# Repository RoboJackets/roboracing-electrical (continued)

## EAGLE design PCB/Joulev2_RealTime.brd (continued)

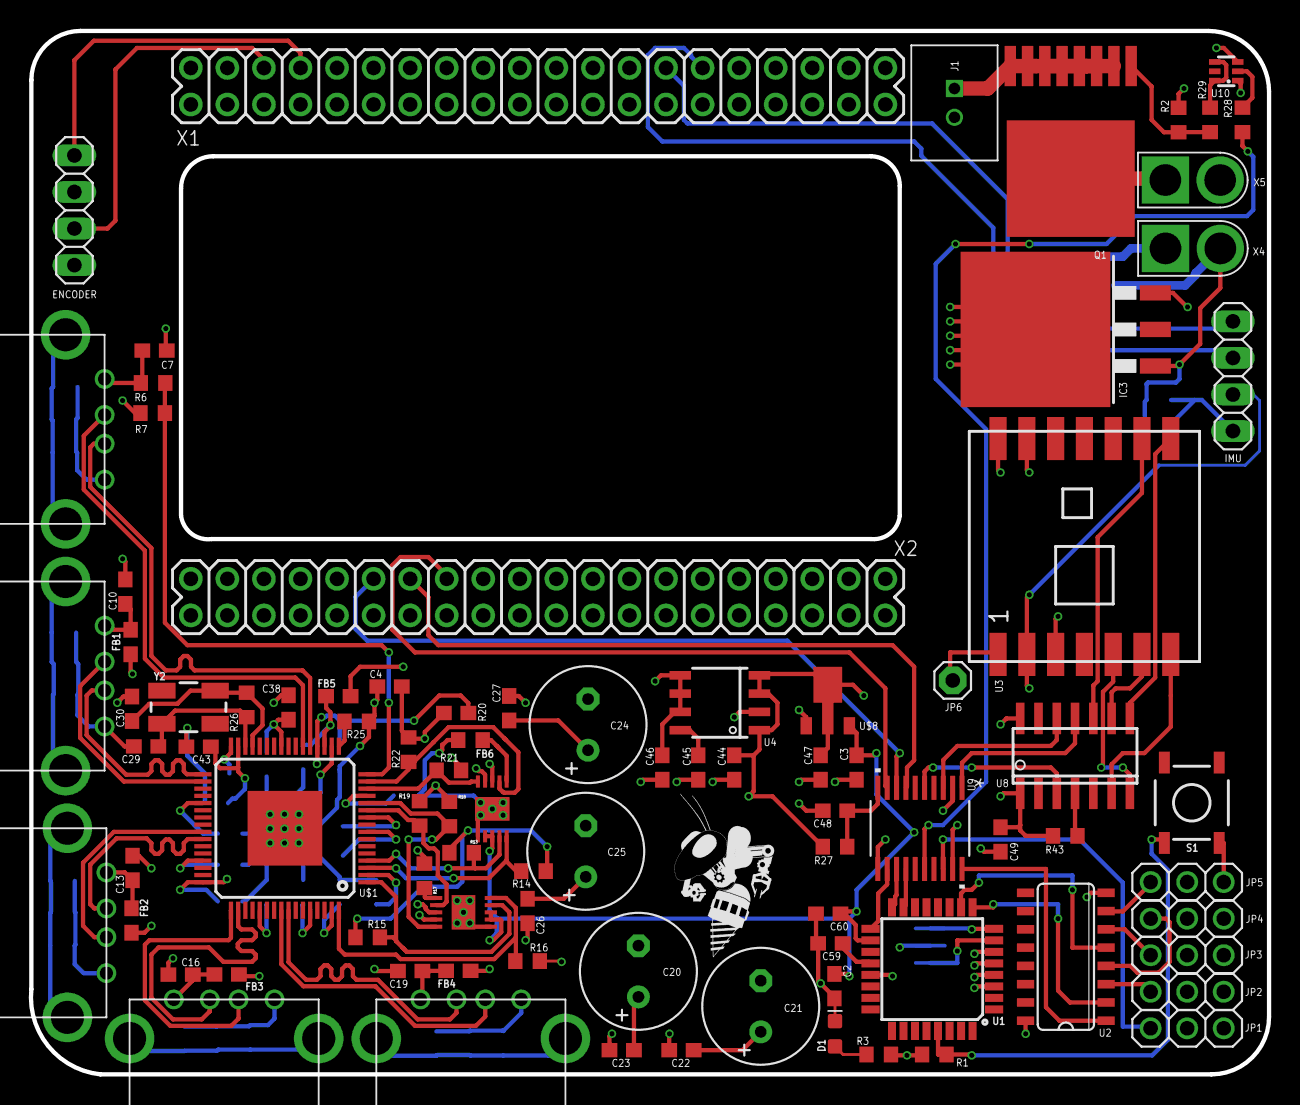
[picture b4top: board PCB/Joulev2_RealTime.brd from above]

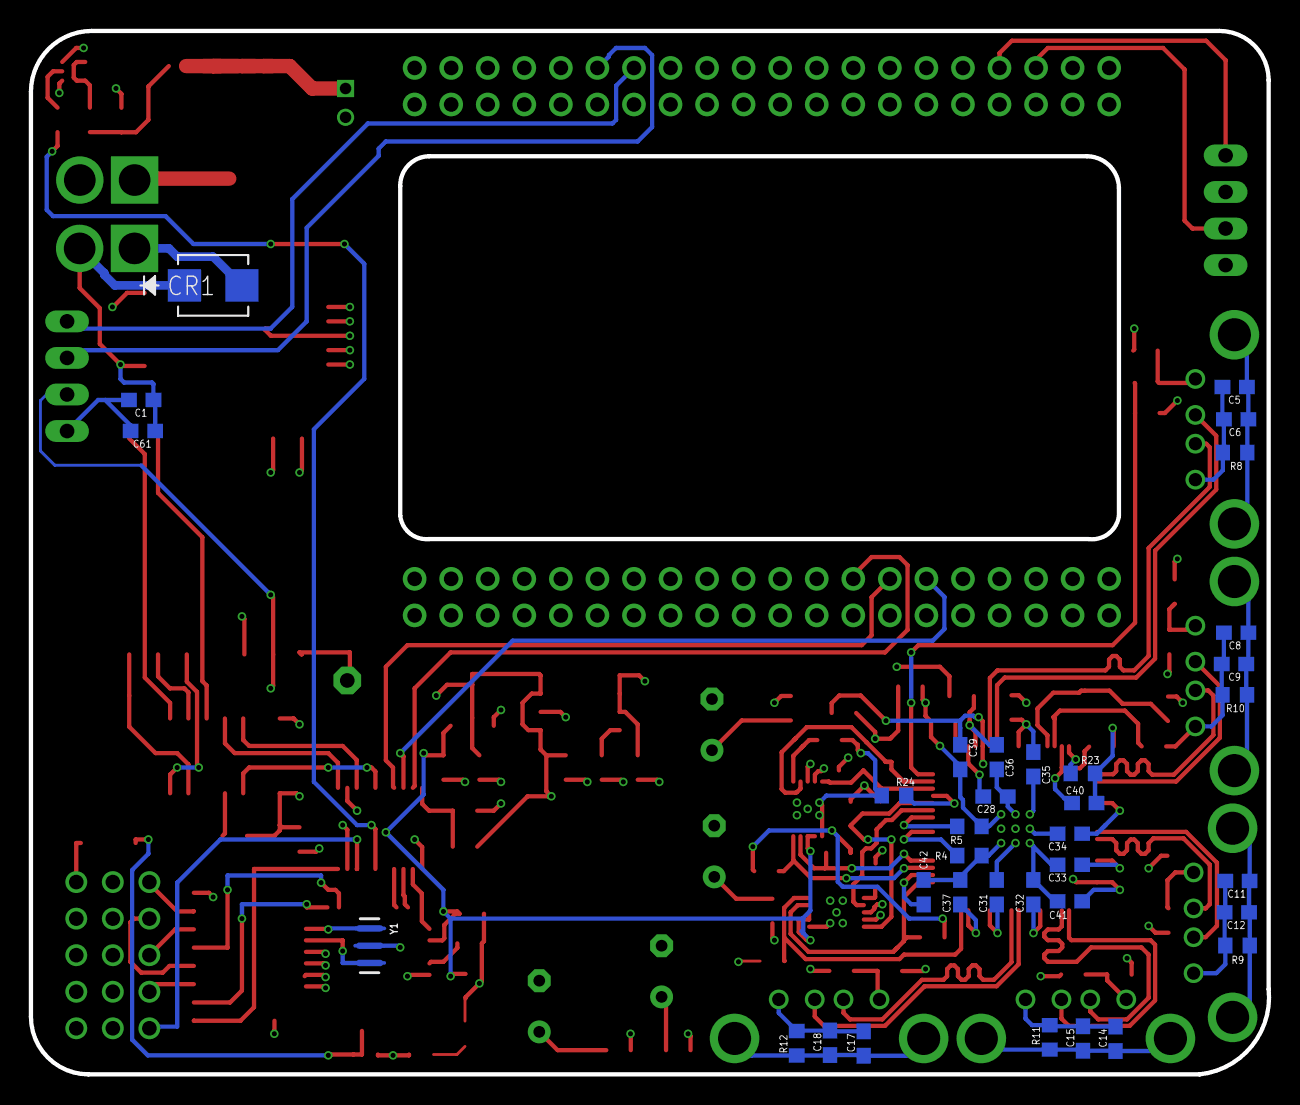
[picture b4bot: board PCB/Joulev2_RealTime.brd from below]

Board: 4 copper layers, 86.0 x 72.5 mm, 125 parts (35 on the bottom side), 94 nets.

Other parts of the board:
U$9: ROBOBUZZ_0.6X

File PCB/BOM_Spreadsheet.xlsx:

Qty | Value | Device | Package | Parts | Description | MANUFACTURER_PART_NUMBER | PINS | PIN_PITCH | PROD_ID | SF_ID | SF_SKU | VALUE | VENDOR | VENDOR PART# | LINK | COST | TOT COST | Notes
3 |  | LED0603 | LED-0603 | D1 | LED (Generic) | LS Q976-NR-1 |  |  |  |  |  |  | Digikey | 475-2512-1-ND | https://www.digikey.com/product-detail/en/osram-opto-semicon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 | 0.26 | 0.78 | Spare 2 ordered
10 |  | PINHD-1X3 | 1X03 | 1, 2, 3, SER, THR | PIN HEADER | M20-9990345 |  |  |  |  |  |  | Digikey | 952-2263-ND | https://www.digikey.com/product-detail/en/harwin-inc/M20-999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 | 0.18 | 1.7999999999999998 | Spare 5 Ordered
5 |  | PINHD-1X4 | 1X04 | ENCODER, IMU | PIN HEADER | 68016-204HLF |  |  |  |  |  |  | Digikey | 609-3319-ND | https://www.digikey.com/product-detail/en/amphenol-fci/68016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 | 0.31 | 1.55 | Spare 3 ordered
40 | 0.1uF | C-USC0603 | C0603 | C2, C5, C9, C10, C12, C13, C15, C16, C18, C19, C22, C23, C26, C27, C28, C31, C3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 | CAPACITOR, American symbol | GRM033R61A104ME15D |  |  |  |  |  |  | Digikey | 490-5405-6-ND | https://www.digikey.com/product-detail/en/murata-electronics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 | 0.17 | 6.8000000000000007 | Spare 11 ordered
3 | 0.22uF | C-USC0603 | C0603 | C1 | CAPACITOR, American symbol | C1608X7R1C224K080AC |  |  |  |  |  |  | Digikey | 445-1318-1-ND | https://www.digikey.com/product-detail/en/tdk-corporation/C1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 | 0.1 | 0.30000000000000004 | Spare 2 ordered
10 | 1.0nF | C-USC0603 | C0603 | C6 | CAPACITOR, American symbol | GRM155R60J102KA01D |  |  |  |  |  |  | Digikey | 490-6285-1-ND | https://www.digikey.com/product-detail/en/murata-electronics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 | 1.0999999999999999E-2 | 0.10999999999999999 | Spare 9 ordered (cheaper than just 3)
10 | 10 | R-US_R0603 | R0603 | R29 | RESISTOR, American symbol | RC0603FR-0710RL |  |  |  |  |  |  | Digikey | 311-10.0HRCT-ND | https://www.digikey.com/product-detail/en/yageo/RC0603FR-071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 | 1.4E-2 | 0.14000000000000001 | Spare 9 ordered (cheaper than just 3)
10 | 10nF | C-USC0603 | C0603 | C45 | CAPACITOR, American symbol | GRM033R71A103KA01D |  |  |  |  |  |  | Digikey | 490-3194-1-ND | https://www.digikey.com/product-detail/en/murata-electronics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 | 2.1000000000000001E-2 | 0.21000000000000002 | Spare 9 ordered (cheaper than just 3)
4 | 1000pF | C-USC0603 | C0603 | C8, C11, C14, C17 | CAPACITOR, American symbol |  |  |  |  |  |  |  | Digikey |  |  |  | 0
9 | 10k | R-US_R0603 | R0603 | R1, R2, R7, R18, R19, R21, R22, R27, R43 | RESISTOR, American symbol |  |  |  |  |  |  |  | Digikey |  |  |  | 0
6 | 10uF | C-USC0603 | C0603 | C3, C4, C7, C38, C43, C61 | CAPACITOR, American symbol |  |  |  |  |  |  |  | Digikey |  |  |  | 0
4 | 150uF | CPOL-USE3.5-8 | E3,5-8 | C20, C21, C24, C25 | POLARIZED CAPACITOR, American symbol |  |  |  |  |  |  |  | Digikey |  |  |  | 0
1 | 16MHz | RESONATOR-16MHZSMD_3.2X1.3 | RESONATOR-SMD-3.2X1.3 | Y1 | 16MHz Resonator |  |  |  | XTAL-08900 |  |  | 16MHz | Digikey |  |  |  | 0
2 | 18pF | C-USC0603 | C0603 | C29, C30 | CAPACITOR, American symbol |  |  |  |  |  |  |  | Digikey |  |  |  | 0
6 | 1M | R-US_R0603 | R0603 | R8, R9, R10, R11, R12, R26 | RESISTOR, American symbol |  |  |  |  |  |  |  | Digikey |  |  |  | 0
1 | 1uF | C-USC0603 | C0603 | C48 | CAPACITOR, American symbol |  |  |  |  |  |  |  | Digikey |  |  |  | 0
1 | 2-PIN_2MM-V | 2-PIN_2MM-V | 2MM-2-V | J1 |  |  | 2 | 2.0 mm |  |  |  |  |  |  |  |  | 0
6 | 220@100MHz | FERRITE_BEAD-0603 | 603 | FB1, FB2, FB3, FB4, FB5, FB6 | Ferrite Bead (blocks, cores, rings, chokes, etc.) |  |  |  | NDUC-07859 |  |  | 30O/1.8A |  |  |  |  | 0
1 | 22uF | C-USC0603 | C0603 | C47 | CAPACITOR, American symbol |  |  |  |  |  |  |  |  |  |  |  | 0
1 | 24MHz | CRYSTAL-24MHZ";CRYSTAL-SMD-5X3.2-4PAD" | Y2 | 24MHz Crystal |  |  |  | XTAL-08298 | COM-08581 |  | 24MHz |  |  |  |  |  | 0
2 | 25.5k | R-US_R0603 | R0603 | R17, R20 | RESISTOR, American symbol |  |  |  |  |  |  |  |  |  |  |  | 0
8 | 4.7k | R-US_R0603 | R0603 | R4, R5, R13, R14, R15, R16, R24, R25 | RESISTOR, American symbol |  |  |  |  |  |  |  |  |  |  |  | 0
2 | 4.7uF | C-USC0603 | C0603 | C44, C46 | CAPACITOR, American symbol |  |  |  |  |  |  |  |  |  |  |  | 0
1 | 500 | R-US_R0603 | R0603 | R28 | RESISTOR, American symbol |  |  |  |  |  |  |  |  |  |  |  | 0
1 | 680 | R-US_R0603 | R0603 | R3 | RESISTOR, American symbol |  |  |  |  |  |  |  |  |  |  |  | 0
1 | 74VHC_MUXSO16 | 74VHC_MUXSO16 | SO16 | U2 |  |  |  |  |  |  |  |  |  |  |  |  | 0
1 | 9.53k | R-US_R0603 | R0603 | R23 | RESISTOR, American symbol |  |  |  |  |  |  |  |  |  |  |  | 0
1 | 90.9k | R-US_R0603 | R0603 | R6 | RESISTOR, American symbol |  |  |  |  |  |  |  |  |  |  |  | 0
1 | ADP1706ARDZ-1.1-R7 | ADP1706ARDZ-1.1-R7 | SOIC8 | U4 |  |  |  |  |  |  |  |  |  |  |  |  | 0
1 | ATMEGA328P_TQFP | ATMEGA328P_TQFP | TQFP32-08 | U1 | Popular 328P in QFP |  |  |  | IC-09069 |  |  | ATMEGA328P_TQFP |  |  |  |  | 0
1 | ATTINY441/841SSU/SSUR | ATTINY441/841SSU/SSUR | SOIC-14 | U8 |  |  |  |  |  |  |  |  |  |  |  |  | 0
1 | AZ1117CR-3.3TRG1DICT-ND | AZ1117CR-3.3TRG1DICT-ND | SOT89R_INFINEON | U$8 |  |  |  |  |  |  |  |  |  |  |  |  | 0
1 | J12HEADER_(JOULE) | J12HEADER_(JOULE) | 2X20 | X1 |  |  |  |  |  |  |  |  |  |  |  |  | 0
1 | J13HEADER_(JOULE) | J13HEADER_(JOULE) | 2X20 | X2 |  |  |  |  |  |  |  |  |  |  |  |  | 0
1 | LM340S-05 | LM340S-05 | TO263-3 | IC3 | Positive VOLTAGE REGULATOR |  |  |  |  |  |  |  |  |  |  |  | 0
1 | MOMENTARY-SWITCH 5.2mm | MOMENTARY-SWITCH-SPST-SMD-5.2MM | TACTILE_SWITCH_SMD_5.2MM | S1 | Momentary Switch (Pushbutton) - SPST |  |  |  | SWCH-08247 |  | COM-08720 |  |  |  |  |  | 0
1 | N_CH_MOSFET_FDLBL260N100 | N_CH_MOSFET_FDLBL260N100 | MO-299A | Q1 |  |  |  |  |  |  |  |  |  |  |  |  | 0
1 | RFM69CW | RFM69CW | RFM69CW-XXXS2 | U3 |  |  |  |  |  |  |  |  |  |  |  |  | 0
1 | SMBJ13CA | SMBJ13CA | SMB | CR1 |  | SMBJ13CA |  |  |  |  |  |  | Bourns Electronics |  |  |  | 0
2 | TPS2561DRCT | TPS2561DRCT | 10-VSON | U$10, U$11 |  |  |  |  |  |  |  |  |  |  |  |  | 0
2 | TRAXXAS-CON | TRAXXAS-CON | TRAXXAS-CON | X4, X5 |  |  |  |  |  |  |  |  |  |  |  |  | 0
1 | TUSB4041 | TUSB4041 | TQFP64-10X10 | U$1 |  |  |  |  |  |  |  |  |  |  |  |  | 0
1 | TXB0108PWR | TXB0108PWR | PW20 | U9 |  | TXB0108PWR |  |  |  |  |  |  | Texas Instruments |  |  |  | 0
5 | USB_TYPE_A | USB_TYPE_A | USB_TYPE_A | U$3, U$4, U$5, U$6, U$7 |  |  |  |  |  |  |  |  |  |  |  |  | 0
1 | ZXGD3009DY | ZXGD3009DY | SOT363 | U10 |  |  |  |  |  |  |  |  |  |  |  |  | 0
1 | antenna | PINHD-1X1 | 1X01 | JP6 | Pin header 1x1 for 0.1 spacing" |  |  |  |  |  |  |  |  |  |  |  | 0

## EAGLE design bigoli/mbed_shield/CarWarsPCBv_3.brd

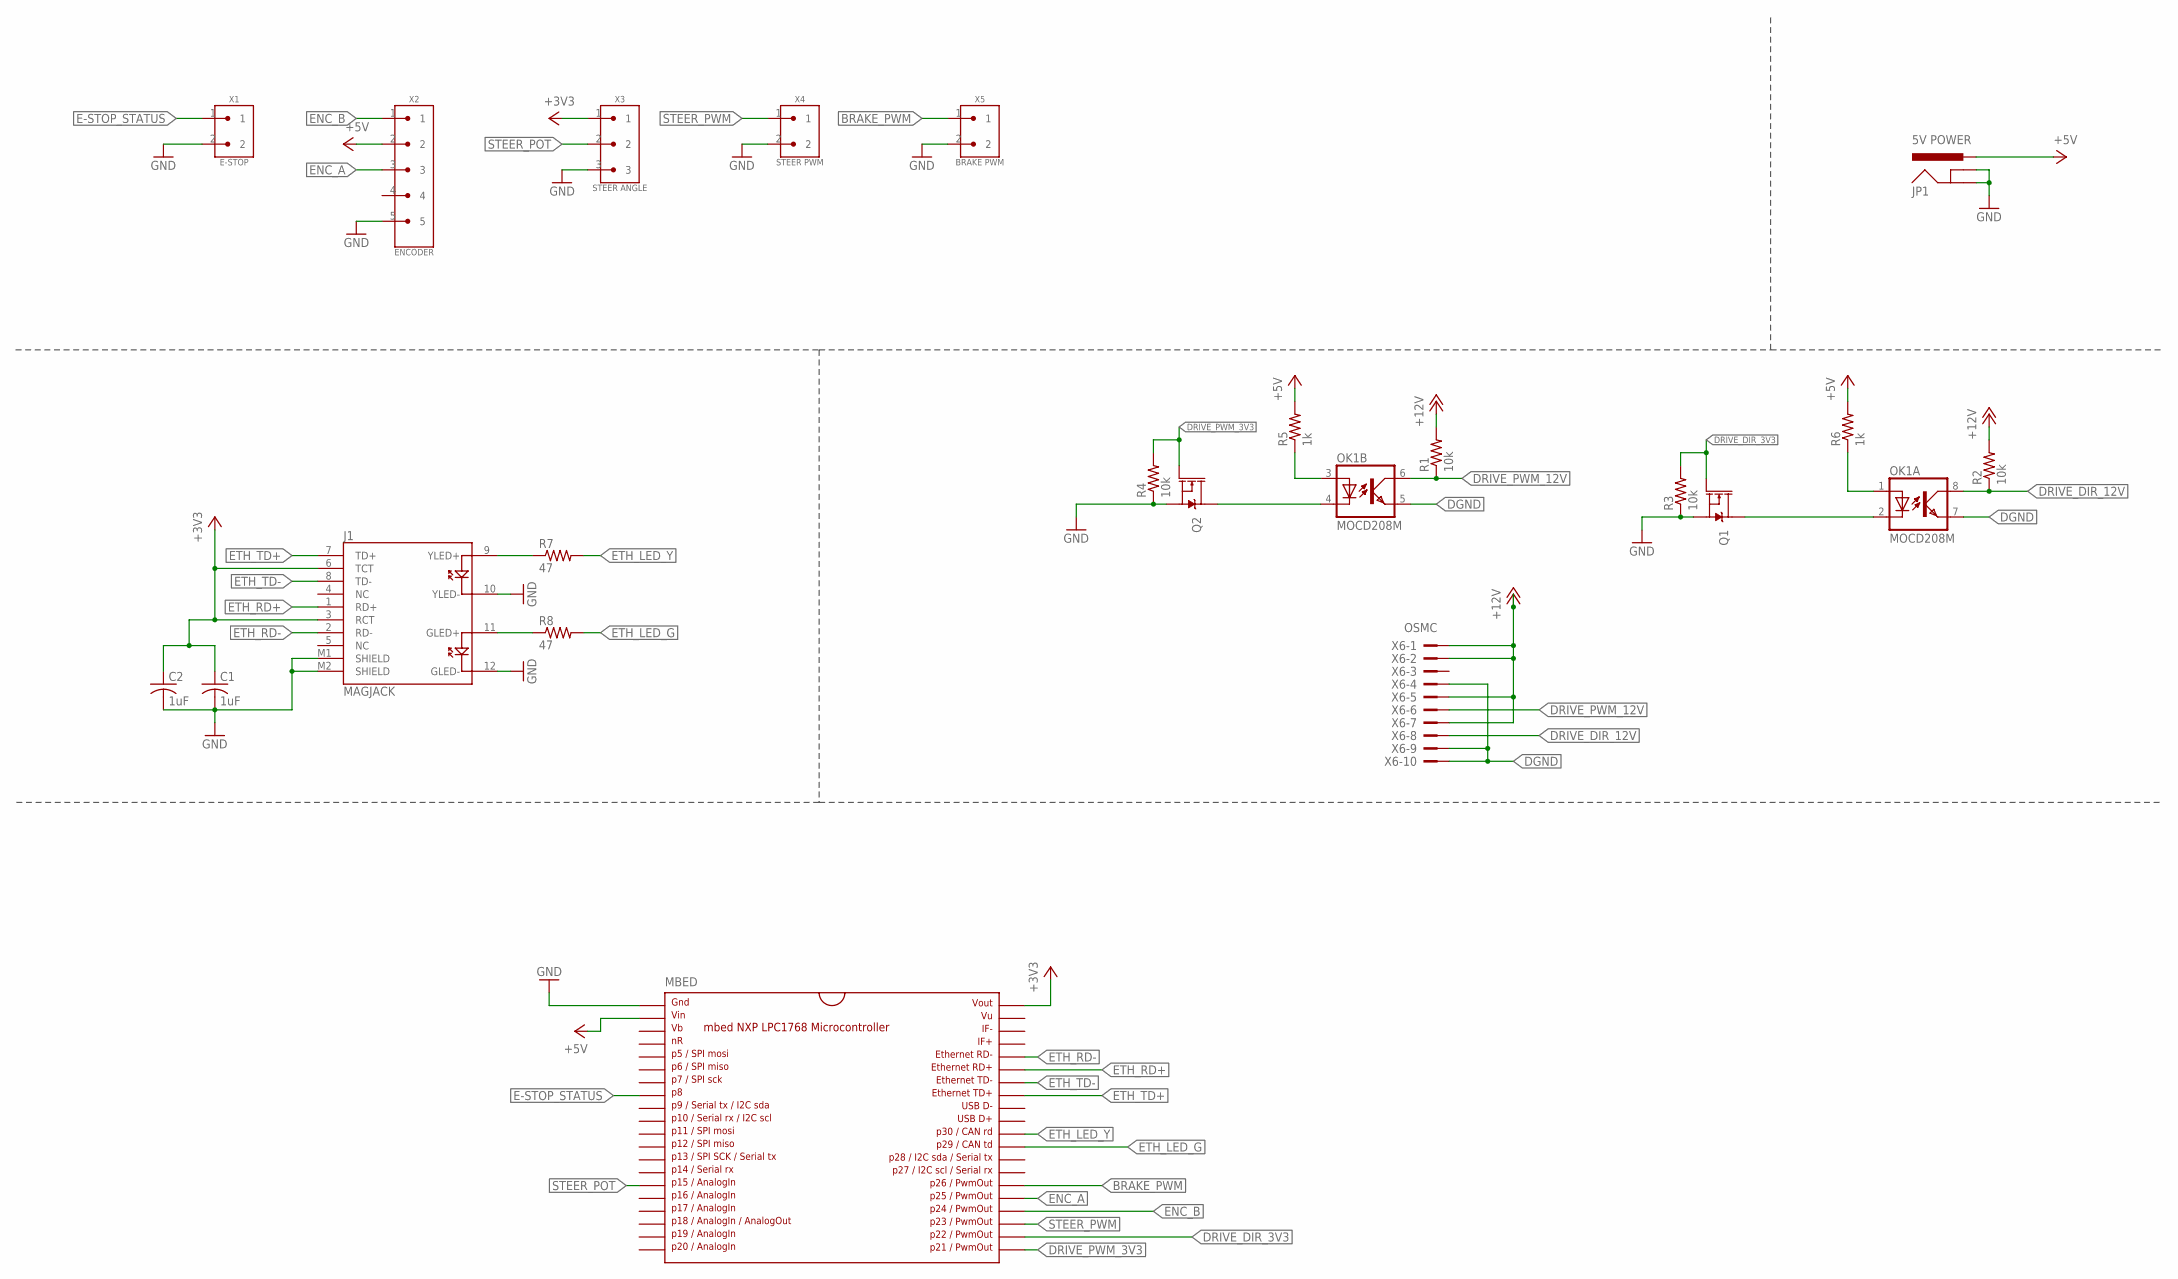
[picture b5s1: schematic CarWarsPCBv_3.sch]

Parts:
C1, C2: 1uF; C0805
J1: MAGJACK
JP1: 5V POWER; POWER_JACK_PTH
MBED: MBED1768; DIL40_0.9
OK1: MOCD208M; SOIC08-FAIRCHILD
Q1, Q2: MOSFET-NCH-BSS138; SOT23-3
R1, R2, R3, R4: 10k; R0603
R5, R6: 1k; R0603
R7, R8: 47; R0603
X1: E-STOP; S2B-EH
X2: ENCODER; S5B-EH
X3: STEER ANGLE; S3B-EH
X4: STEER PWM; S2B-EH
X5: BRAKE PWM; S2B-EH
X6: OSMC; PAK100/2500-10

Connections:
+3V3: C1.1, C2.1, J1.3 (RCT), J1.6 (TCT), MBED.40, X3.1
+5V: JP1.PWR, MBED.2, R5.2, R6.2, X2.2
+12V: R1.2, R2.2, X6.1, X6.2, X6.5, X6.7
BRAKE_PWM: MBED.26, X5.1
DGND: OK1.5 (EMIT), OK1.7 (EMIT), X6.4, X6.9, X6.10
DRIVE_DIR_3V3: MBED.22, Q1.1 (G), R3.2
DRIVE_DIR_12V: OK1.8 (COL), R2.1, X6.8
DRIVE_PWM_3V3: MBED.21, Q2.1 (G), R4.2
DRIVE_PWM_12V: OK1.6 (COL), R1.1, X6.6
E-STOP_STATUS: MBED.8, X1.1
ENC_A: MBED.25, X2.3
ENC_B: MBED.24, X2.1
ETH_LED_G: MBED.29, R8.2
ETH_LED_Y: MBED.30, R7.2
ETH_RD+: J1.1 (RD+), MBED.35
ETH_RD-: J1.2 (RD-), MBED.36
ETH_TD+: J1.7 (TD+), MBED.33
ETH_TD-: J1.8 (TD-), MBED.34
GND: C1.2, C2.2, J1.10 (YLED-), J1.12 (GLED-), J1.M1 (SHIELD), J1.M2 (SHIELD), JP1.GND, JP1.GNDBREAK, MBED.1, Q1.2 (S), Q2.2 (S), R3.1, R4.1, X1.2, X2.5, X3.3, X4.2, X5.2
unnamed: OK1.2 (C), Q1.3 (D)
unnamed: OK1.4 (C), Q2.3 (D)
unnamed: OK1.3 (A), R5.1
unnamed: OK1.1 (A), R6.1
unnamed: J1.9 (YLED+), R7.1
unnamed: J1.11 (GLED+), R8.1
STEER_POT: MBED.15, X3.2
STEER_PWM: MBED.23, X4.1

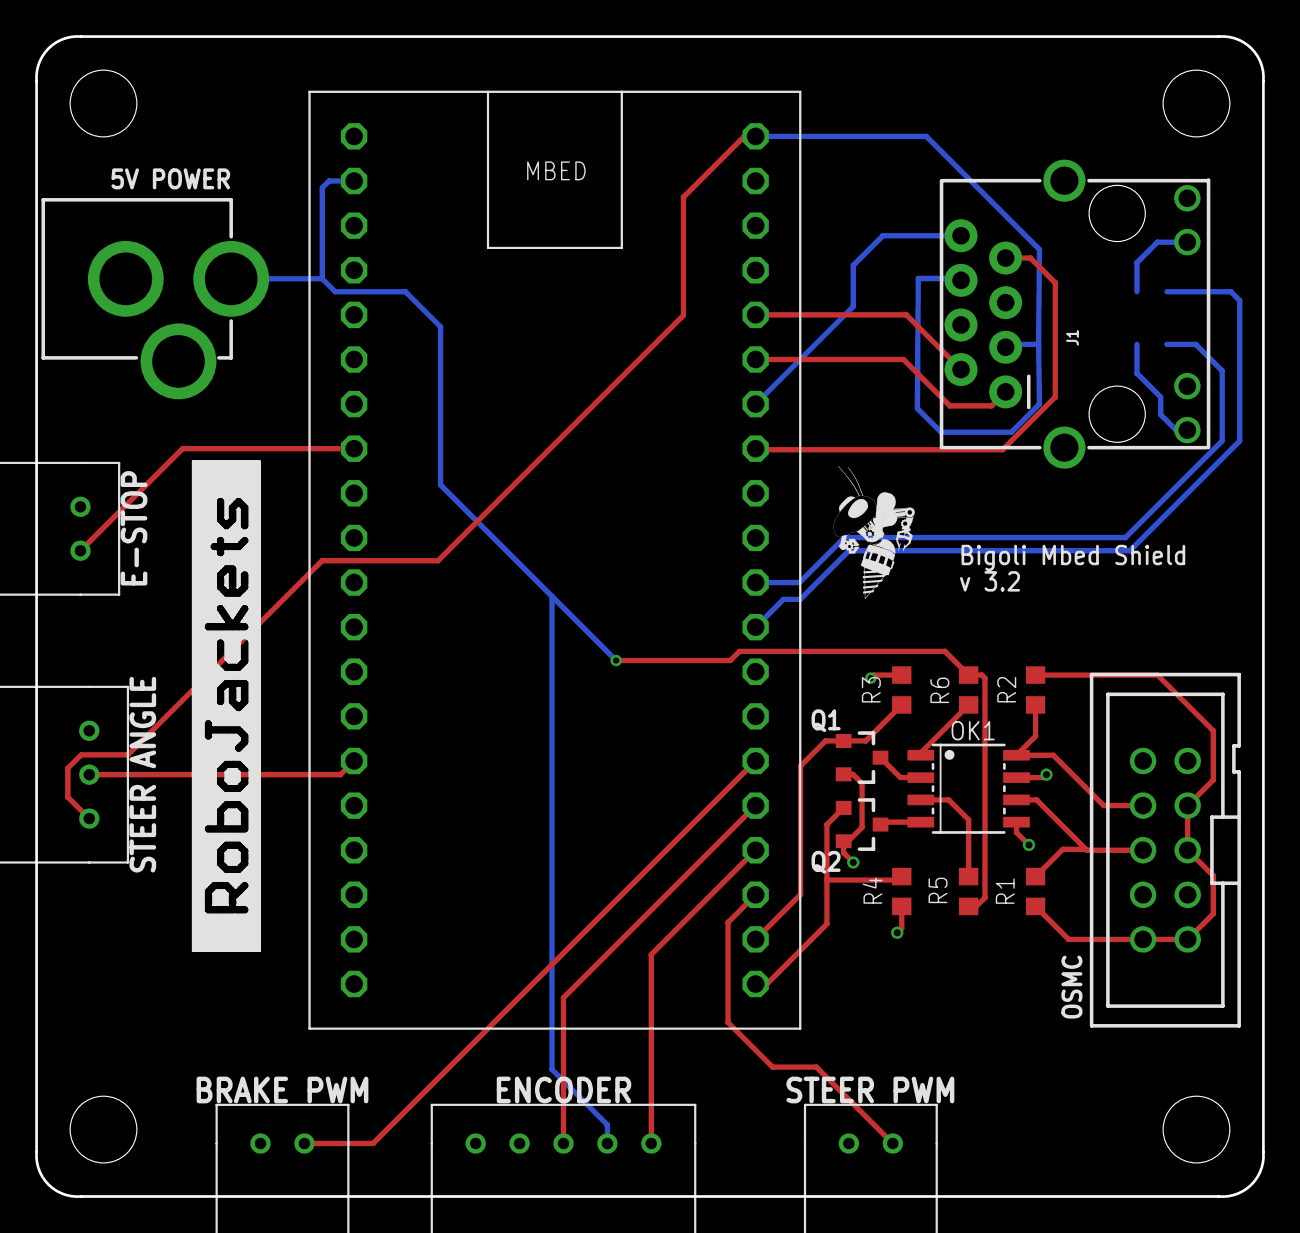
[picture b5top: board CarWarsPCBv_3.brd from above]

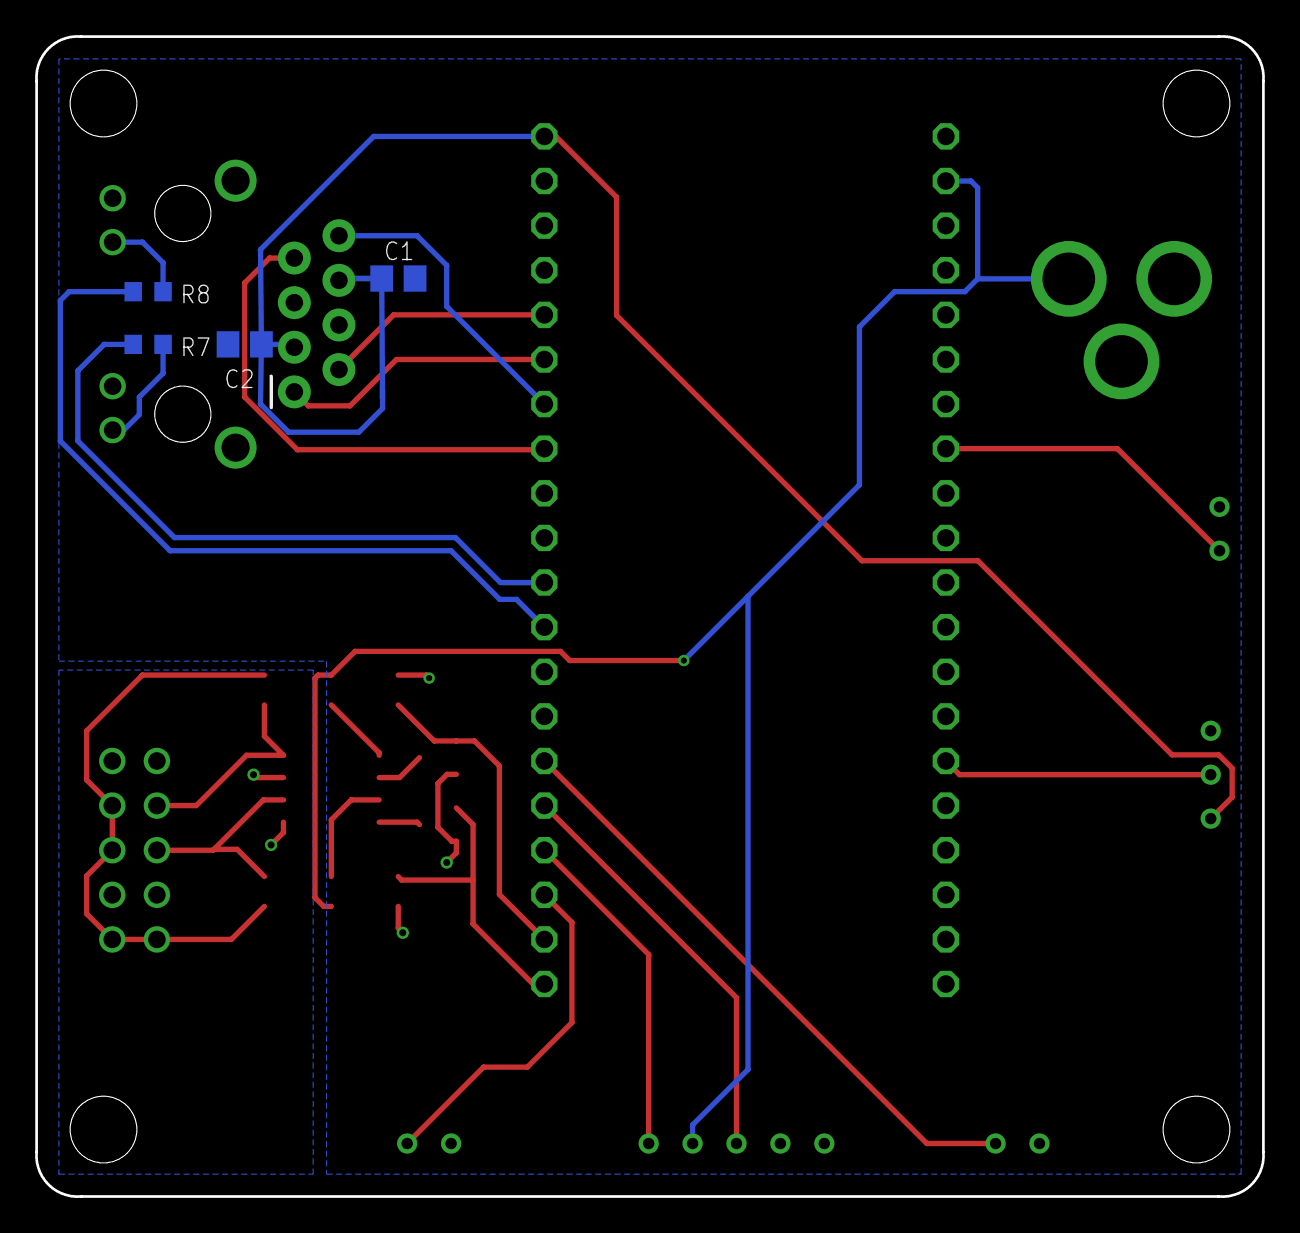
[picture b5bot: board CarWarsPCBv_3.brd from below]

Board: 2 copper layers, 69.9 x 66.1 mm, 24 parts (4 on the bottom side), 27 nets.

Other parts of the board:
U$1: ROBOBUZZ_0.4X
U$2: ROBOJACKETS
